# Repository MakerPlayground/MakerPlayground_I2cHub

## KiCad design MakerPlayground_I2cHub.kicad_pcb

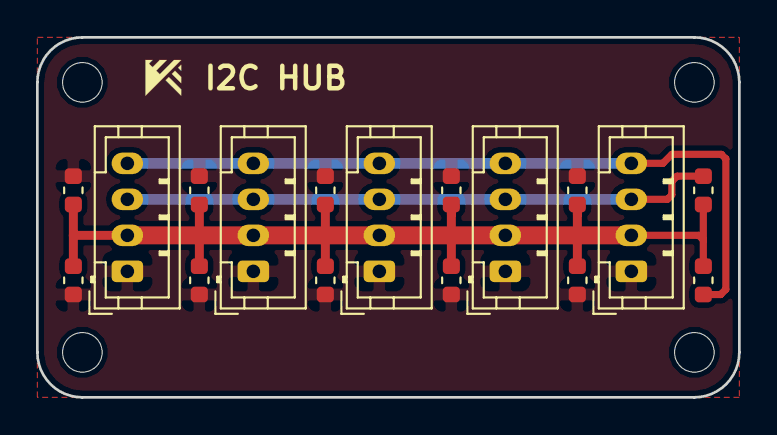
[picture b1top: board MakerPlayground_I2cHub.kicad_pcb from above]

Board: 2 copper layers, 39.0 x 20.0 mm, 17 parts (0 on the bottom side), 4 nets.

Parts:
C1, C3, C4, C5, C6: 0.1uF; C_0603_1608Metric
C2, C7, C8, C9, C10: 1uF; C_0603_1608Metric
J1, J2, J3, J4, J5: Conn_01x04; JST_PH_B4B-PH-K_1x04_P2.00mm_Vertical
R1, R2: 10K; R_0603_1608Metric

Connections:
GND: C1.2, C2.2, C3.2, C4.2, C5.2, C6.2, C7.2, C8.2, C9.2, C10.2, J1.1, J2.1, J3.1, J4.1, J5.1
SCL: J1.4, J2.4, J3.4, J4.4, J5.4, R1.2
SDA: J1.3, J2.3, J3.3, J4.3, J5.3, R2.2
VCC: C1.1, C2.1, C3.1, C4.1, C5.1, C6.1, C7.1, C8.1, C9.1, C10.1, J1.2, J2.2, J3.2, J4.2, J5.2, R1.1, R2.1

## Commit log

2018-11-07 The first commit of MakerPlayground_I2cHub.
2018-11-07 Add more capacitors & new capacitors, resistors alignment.
2018-11-07 Finalize.
